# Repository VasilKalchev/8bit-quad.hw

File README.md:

# 8bit-quad

Flight controller **PCB** for a custom-built quadcopter based on the ATmega328
microcontroller. An IMU, an nRF24L01+ radio and four ESC outputs on a 113 mm
octagon shaped to the top plate of an F450 frame.

It was etched at home, populated, flown, and retired. This repository is an
archive of it, not a design anyone is expected to build. [The firmware that
ran on it](https://github.com/VasilKalchev/8bit-quad) is in its own
repository.

<sub>The board on the frame with an FTDI adapter attached. The remote is on
the right, on protoboard. It never had a PCB; what it had to provide is in
<a href="rc/">rc/</a>.</sub>

<table>
<tr>
<td width="50%"></td>
<td width="50%"></td>
</tr>
<tr>
<td align="center"><sub>schematic, click for the PDF</sub></td>
<td align="center"><sub>board</sub></td>
</tr>
</table>

```
fc/          KiCad 10 project, symbols and footprints included
  _export/   schematic and board images
  bom.txt    62 components
rc/          what the remote had to provide
gallery/     photographs
```

Everything the project needs is inside it. There are no dependencies on
installed libraries.

## The board

**The outline** is a 113 mm octagon because the board was originally meant to
*be* the F450's top plate rather than sit on it. A load-bearing flight
controller: the arms bolt through it, every landing is absorbed by the PCB,
the frame's vibration is piped straight into the IMU with nothing in between,
and any crash that would have cracked a plate worth a couple of euros instead
cracks the one part carrying all the electronics. Obvious in hindsight. Also
in foresight, to be fair.

The shape stayed regardless, and the board ended up bolted above the plate
like every other flight controller ever made.

Pin names below are the ones the firmware uses.

**The microcontroller** is an ATmega328P-PU in a DIP-28 socket with a 16 MHz
crystal, programmed over either an AVR ISP header or an FTDI header, with a
restart button next to it.

**The IMU** is an MPU6050 or MPU9250 breakout on I2C. There are two header
footprints for it, 1x8 and 1x5, so either of the two common module shapes
fits. Its interrupt lands on `PD2`. The outline drawn around it is an
anti-vibration plate, drawn when it was still meant to carry the IMU module
and nothing else. It ended up carrying the whole flight controller. So the
vibration problem was understood, and then solved by moving it one level up.

**The radio** is an nRF24L01+ PA/LNA module on hardware SPI, with `CE` on
`PD7`, `CSN` on `PB0` and the interrupt on `PC0`. The firmware's last revision
abandoned it for a PPM receiver, which takes over `PD2`.

**The ESC outputs** are four 3-pin headers labelled by frame position: `TL` on
`PD5`, `TR` on `PB2`, `BL` on `PD6`, `BR` on `PB1`. All four are hardware PWM
outputs, two on timer 0 and two on timer 1. Freeing timer 0 for that is why
the firmware ships its own Arduino core, which moves `millis()` onto timer 2.

**Power** arrived on a JST connector behind a 2 A PPTC and a MOSFET for
reverse polarity, then a 7805 and a TS1117 gave 5 V and 3.3 V. Battery voltage
reached `PC3` through 110k and 20k over 9k1, which the schematic notes as
`Vout = Vbatt * 0.06542056`.

**Indication** is a signal LED on `PC2` and a warning LED on `PC1`, plus two
low side MOSFETs switching an arm-LED header on `PD3` and a lamp header on
`PD4`.

Two measurements from a PicoScope in March 2022, on the built board: the ESC
drive edges rose in 11.2 ns at 5.065 V, and the IMU's I2C lines in 125 ns at
3.542 V.

## Etched at home

There are no gerbers and never were. The copper layers were printed onto
transparency and the board was etched by photoresist, so its rules are
generous: 18 mil clearance, 16 mil minimum track, 0.8 mm minimum drill. There
is [a video of the etching](https://youtu.be/nzKjSb2GAe4).

<sub>Etched, still purple from the photoresist, before drilling. The clearest
record of the artwork that exists.</sub>

> [!NOTE]
> DRC reports three errors, all on `J1P0`, the JST battery connector, whose
> pads and holes break the board's own rules. That is inherent to the
> footprint and predates the KiCad conversion; the board was built and flown
> that way. The rest is cosmetic silkscreen and thermal relief warnings.
> Connectivity is clean, with zero unconnected items once the zones are
> filled.

## History

This board is v2. The first flight controller was an Arduino Nano and an
nRF24L01+ hand wired on protoboard, and it is the reason this one is lettered
`Flight Controller v2.0`.

<sub>v1, the protoboard flight controller this board replaced. Its IMU
module is missing here.</sub>

It was drawn in Eagle. Autodesk stopped developing standalone Eagle in 2024
and folded it into Fusion, so the design was converted to KiCad in 2026. The
original Eagle files are in the first commit of this repository and nowhere
else.

## Licence

Copyright Vasil Kalchev 2017

Licensed under CERN-OHL-P v2 or later. You may redistribute and modify this
source and make products using it under the terms of the
[CERN-OHL-P v2](https://ohwr.org/cern_ohl_p_v2.txt). This source is
distributed WITHOUT ANY EXPRESS OR IMPLIED WARRANTY, INCLUDING OF
MERCHANTABILITY, SATISFACTORY QUALITY AND FITNESS FOR A PARTICULAR PURPOSE.
Please see the CERN-OHL-P v2 for applicable conditions.

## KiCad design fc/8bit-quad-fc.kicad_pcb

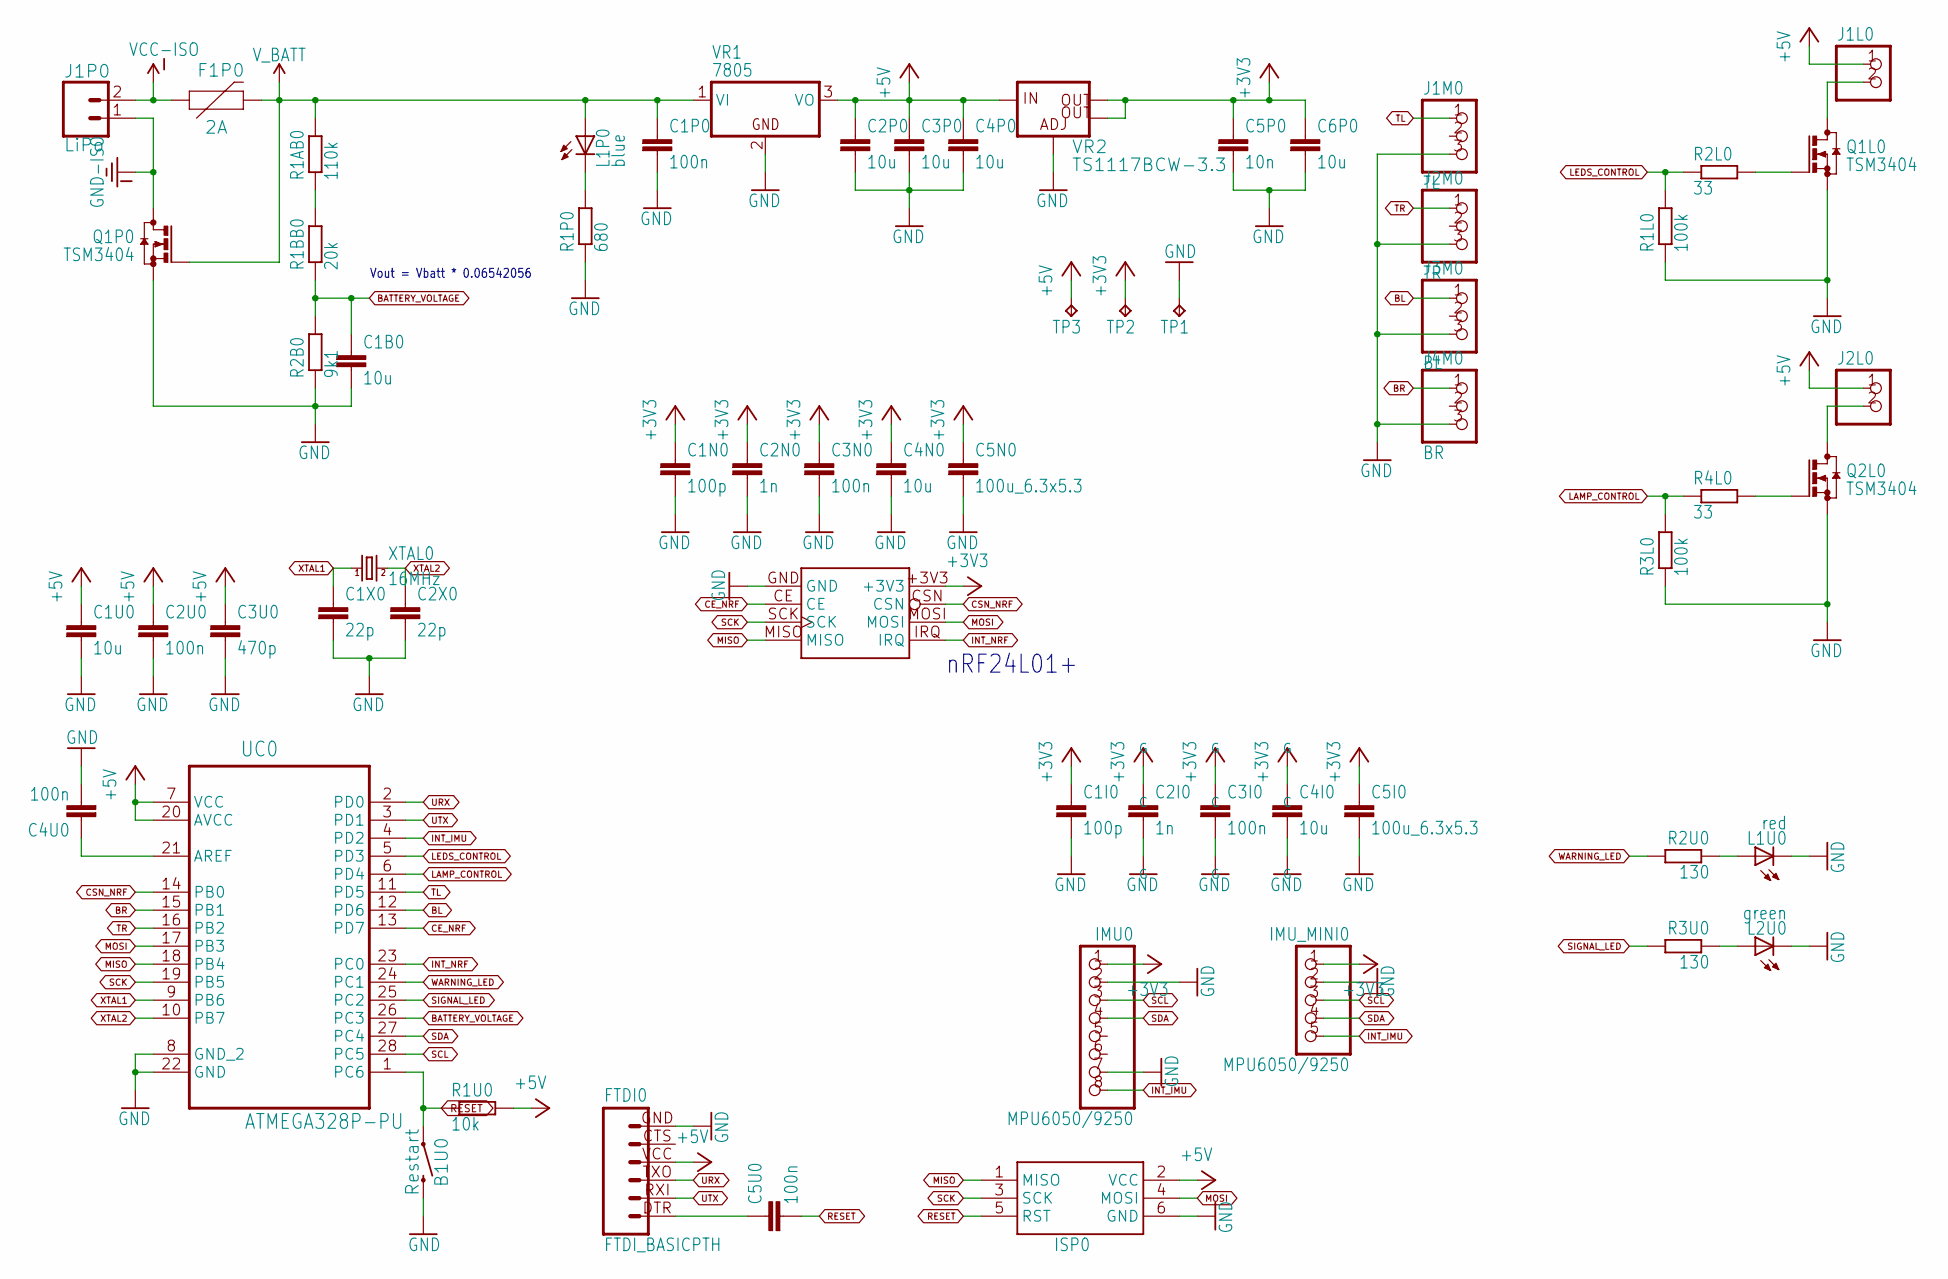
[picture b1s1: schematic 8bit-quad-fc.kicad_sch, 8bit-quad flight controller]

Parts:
B1U0: Restart; TACTILE_SWITCH_PTH_6.0MM
C1B0, C1U0, C2P0, C3P0, C4I0, C4N0, C4P0, C6P0: 10u; C1206
C1I0, C1N0: 100p; C1206
C1P0, C2U0, C3I0, C3N0, C4U0, C5U0: 100n; C1206
C1X0, C2X0: 22p; C1206
C2I0, C2N0: 1n; C1206
C3U0: 470p; C1206
C5I0, C5N0: 100u_6.3x5.3; C3225
C5P0: 10n; C1206
F1P0: 2A; 1206
FTDI0: FTDI_BASICPTH; FTDI_BASIC
IMU0: MPU6050/9250; 1X08
IMU_MINI0: MPU6050/9250; 1X05
ISP0: AVRISP-6; AVRISP
J1L0, J2L0: PINHD-1X2/90; 1X02_90
J1M0: TL; 1X03_90
J1P0: LiPo; JST-2-PTH
J2M0: TR; 1X03_90
J3M0: BL; 1X03_90
J4M0: BR; 1X03_90
L1P0: blue; 1206
L1U0: red; 1206
L2U0: green; 1206
NRF24L01+0: nRF24L01+; NRF24L01+_PA_LNA_SMD
Q1L0, Q1P0, Q2L0: TSM3404; SOT23
R1AB0: 110k; R1206
R1BB0: 20k; R1206
R1L0, R3L0: 100k; R1206
R1P0: 680; R1206
R1U0: 10k; R1206
R2B0: 9k1; R1206
R2L0, R4L0: 33; R1206
R2U0, R3U0: 130; R1206
TP1: 0V; TP10SQ
TP2: 3.3V; TP10SQ
TP3: 5.0V; TP10SQ
UC0: ATMEGA328P-PU; DIP254P762X457-28; MPN ATMEGA328P-PU
VR1: 7805; TO220V
VR2: TS1117BCW-3.3; SOT223
XTAL0: 16MHz; HC49_S

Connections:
+3V3: C1I0.1, C1N0.1, C2I0.1, C2N0.1, C3I0.1, C3N0.1, C4I0.1, C4N0.1, C5I0.1, C5N0.1, C5P0.1, C6P0.1, IMU0.1, IMU_MINI0.1, NRF24L01+0.+3V3, TP2.TP, VR2.2 (OUT), VR2.4 (OUT)
+5V: C1U0.1, C2P0.1, C2U0.1, C3P0.1, C3U0.1, C4P0.1, FTDI0.VCC (4), ISP0.2 (VCC), J1L0.1, J2L0.1, R1U0.2, TP3.TP, UC0.7 (VCC), UC0.20 (AVCC), VR1.3 (VO), VR2.3 (IN)
BATTERY_VOLTAGE: C1B0.1, R1BB0.1, R2B0.2, UC0.26 (PC3)
BL: J3M0.1, UC0.12 (PD6)
BR: J4M0.1, UC0.15 (PB1)
CE_NRF: NRF24L01+0.CE, UC0.13 (PD7)
CSN_NRF: NRF24L01+0.CSN, UC0.14 (PB0)
GND: B1U0.3 (2), C1B0.2, C1I0.2, C1N0.2, C1P0.2, C1U0.2, C1X0.2, C2I0.2, C2N0.2, C2P0.2, C2U0.2, C2X0.2, C3I0.2, C3N0.2, C3P0.2, C3U0.2, C4I0.2, C4N0.2, C4P0.2, C4U0.2, C5I0.2, C5N0.2, C5P0.2, C6P0.2, FTDI0.GND (6), IMU0.2, IMU0.7, IMU_MINI0.2, ISP0.6 (GND), J1M0.3, J2M0.3, J3M0.3, J4M0.3, L1U0.C, L2U0.C, NRF24L01+0.GND, Q1L0.2 (S), Q1P0.2 (S), Q2L0.2 (S), R1L0.1, R1P0.1, R2B0.1, R3L0.1, TP1.TP, UC0.8 (GND_2), UC0.22 (GND), VR1.2 (GND), VR2.1 (ADJ)
GND-ISO: J1P0.1, Q1P0.3 (D)
INT_IMU: IMU0.8, IMU_MINI0.5, UC0.4 (PD2)
INT_NRF: NRF24L01+0.IRQ, UC0.23 (PC0)
LAMP_CONTROL: R3L0.2, R4L0.1, UC0.6 (PD4)
LAMP_SINK: J2L0.2, Q2L0.3 (D)
LEDS_CONTROL: R1L0.2, R2L0.1, UC0.5 (PD3)
LEDS_SINK: J1L0.2, Q1L0.3 (D)
MISO: ISP0.1 (MISO), NRF24L01+0.MISO, UC0.18 (PB4)
MOSI: ISP0.4 (MOSI), NRF24L01+0.MOSI, UC0.17 (PB3)
unnamed: L2U0.A, R3U0.1
unnamed: R1AB0.1, R1BB0.2
unnamed: L1U0.A, R2U0.1
unnamed: Q1L0.1 (G), R2L0.2
unnamed: Q2L0.1 (G), R4L0.2
unnamed: L1P0.C, R1P0.2
unnamed: C4U0.1, UC0.21 (AREF)
unnamed: C5U0.1, FTDI0.DTR (1)
RESET: B1U0.1, C5U0.2, ISP0.5 (RST), R1U0.1, UC0.1 (PC6)
SCK: ISP0.3 (SCK), NRF24L01+0.SCK, UC0.19 (PB5)
SCL: IMU0.3, IMU_MINI0.3, UC0.28 (PC5)
SDA: IMU0.4, IMU_MINI0.4, UC0.27 (PC4)
SIGNAL_LED: R3U0.2, UC0.25 (PC2)
TL: J1M0.1, UC0.11 (PD5)
TR: J2M0.1, UC0.16 (PB2)
URX: FTDI0.TXO (3), UC0.2 (PD0)
UTX: FTDI0.RXI (2), UC0.3 (PD1)
VCC-ISO: F1P0.1, J1P0.2
V_BATT: C1P0.1, F1P0.2, L1P0.A, Q1P0.1 (G), R1AB0.2, VR1.1 (VI)
WARNING_LED: R2U0.2, UC0.24 (PC1)
XTAL1: C1X0.1, UC0.9 (PB6), XTAL0.1
XTAL2: C2X0.1, UC0.10 (PB7), XTAL0.2

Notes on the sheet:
Vout = Vbatt * 0.06542056
nRF24L01+

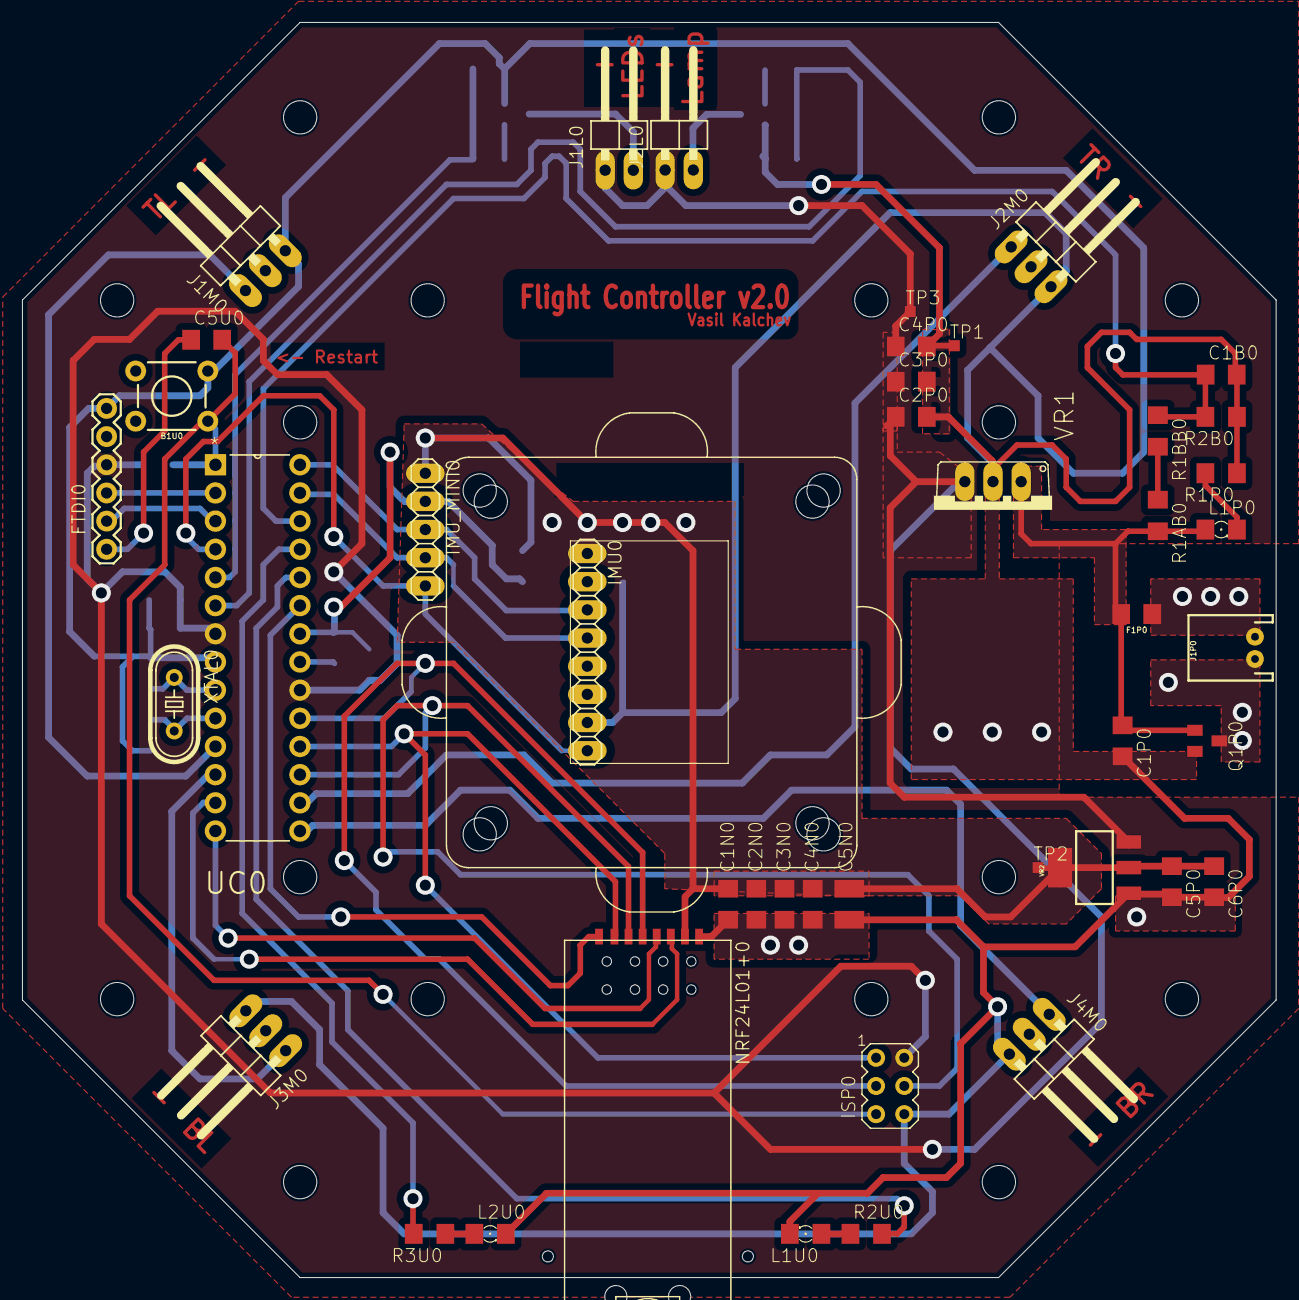
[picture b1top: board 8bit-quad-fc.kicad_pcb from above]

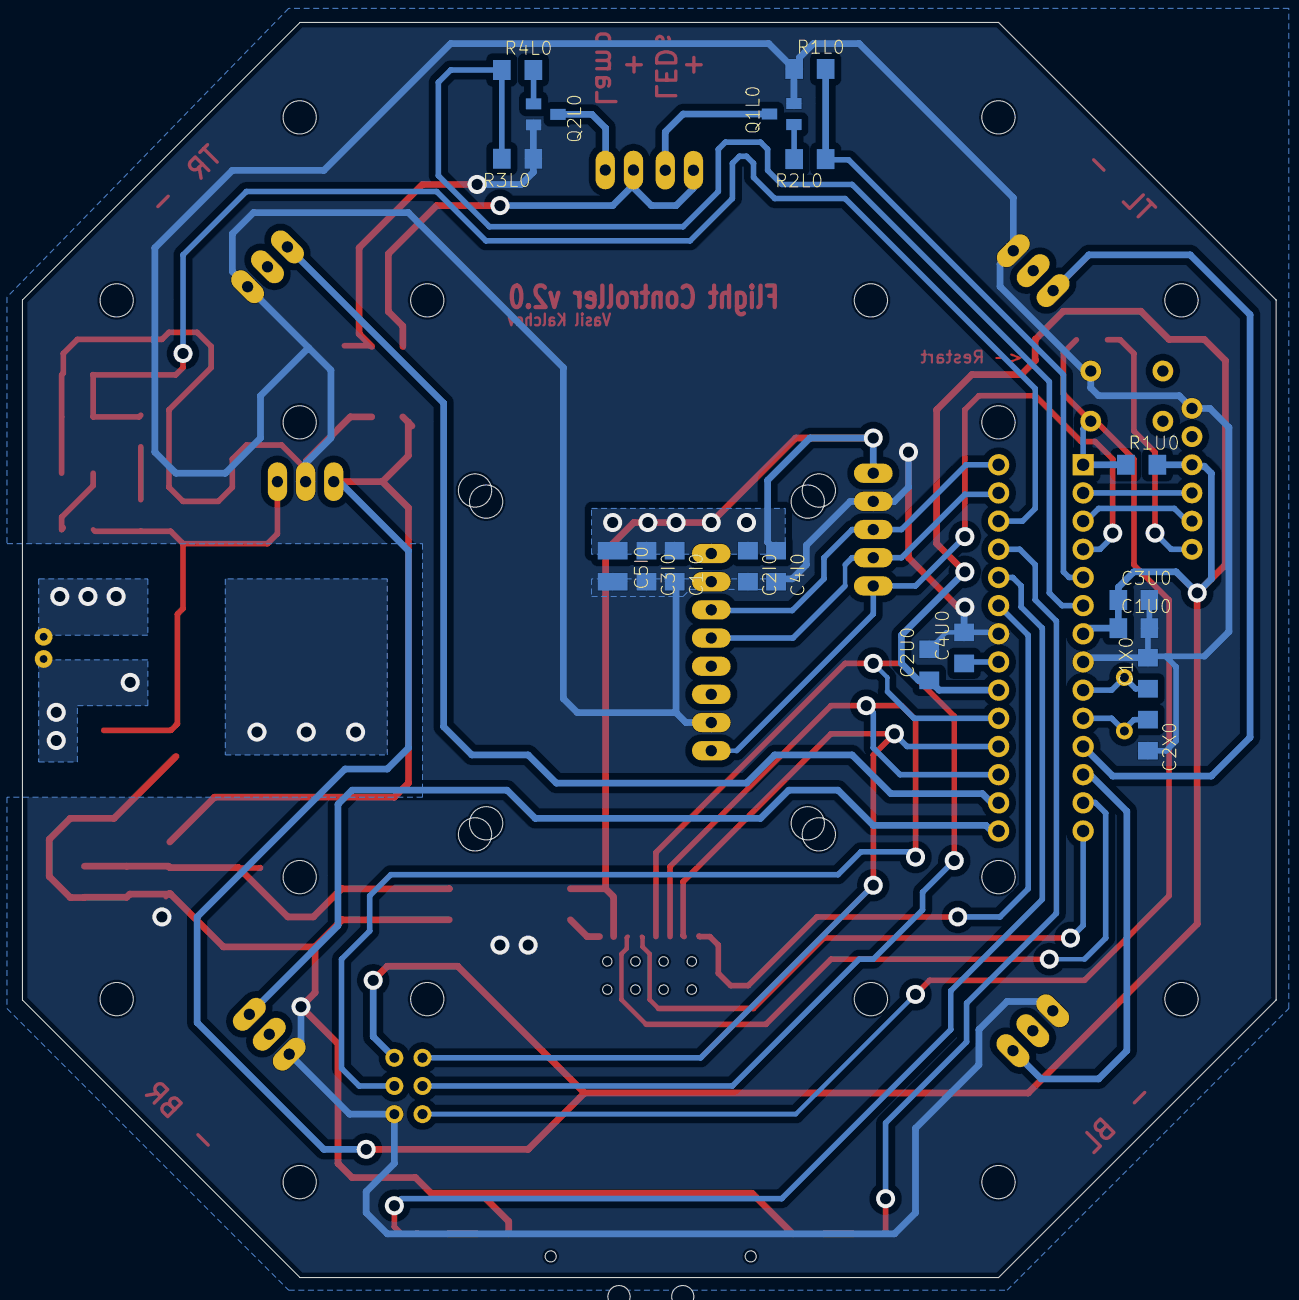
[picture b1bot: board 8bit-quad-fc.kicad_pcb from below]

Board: 2 copper layers, 113.0 x 113.2 mm, 66 parts (18 on the bottom side), 39 nets.

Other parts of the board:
H1, H2: 1 mm hole; HOLE_1MM
U$2: F450_TOP_PLATE
U$3: ANTI-VIBRATION_PLATE

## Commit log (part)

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2017-12-04 Flight controller board, drawn in Eagle and etched at home
    Two layer, 113 mm octagon cut to sit on the top plate of an F450 frame.
    ATmega328P at 16 MHz with an nRF24L01+ PA/LNA module, an MPU6050 or MPU9250
    on either an 8 pin or a 5 pin header, and four 3 pin ESC outputs labelled by
    frame position.
    Power comes in on a JST connector behind a 2 A PPTC and a MOSFET for reverse
    polarity, then a 7805 and a TS1117 for 5 V and 3.3 V. Battery voltage reaches
2018-03-07 Photographs of the etched board
    20180117_133531 is the populated board on the frame, powered, with an FTDI
    adapter attached and the nRF24 and IMU modules seated.
    20180307_234316 is a bare board straight on, still purple from the
    photoresist, before drilling and populating. It is the clearest surviving
    record of the artwork: the octagon, the TL, TR, BL and BR motor labels, the
    Restart, LEDs and Lamp legends, and the title block reading Flight Controller
